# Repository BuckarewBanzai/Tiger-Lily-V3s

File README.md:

# Tiger-Lily-V3s
A breakout board for the Allwinner V3s SOC

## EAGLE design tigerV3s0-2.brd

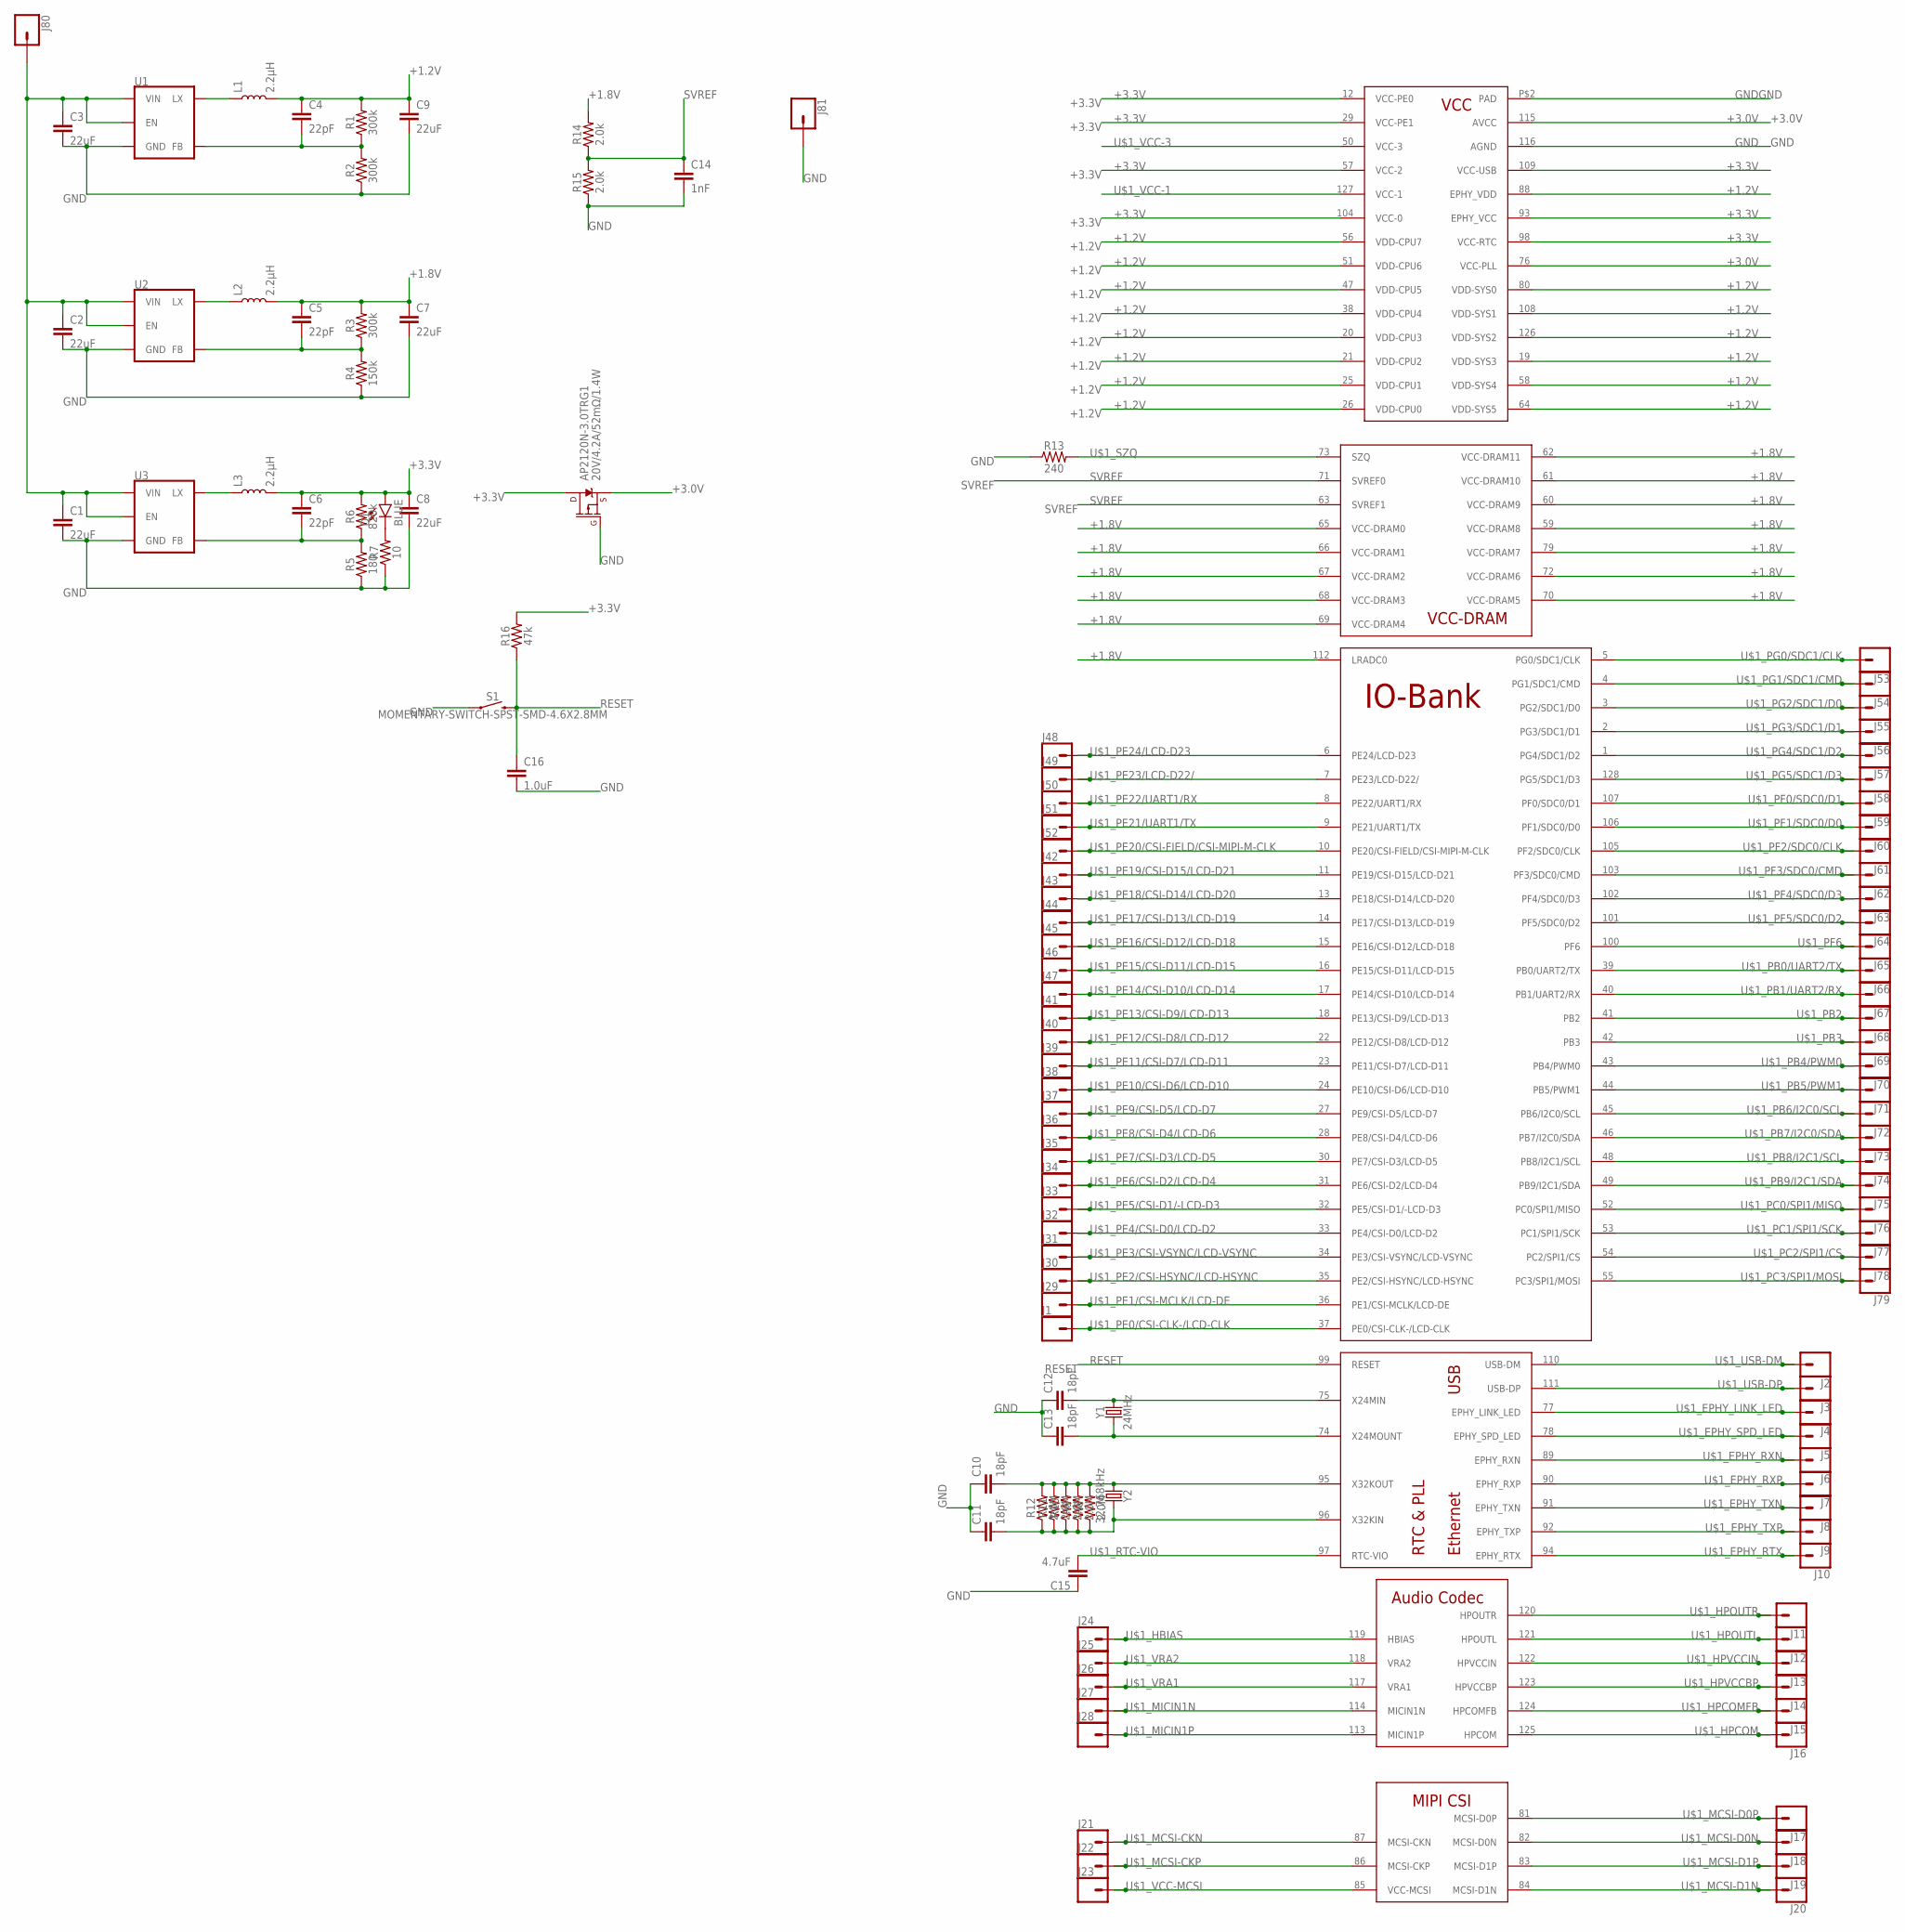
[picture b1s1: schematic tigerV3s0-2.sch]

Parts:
AP2120N-3.0TRG1: 20V/4.2A/52mΩ/1.4W; SOT23-3
C1, C2, C3, C7, C8, C9: 22uF; 0805
C4, C5, C6: 22pF; 0603
C10, C11, C12, C13: 18pF; 0603
C14: 1nF; 0603
C15: 4.7uF; 0603
C16: 1.0uF; 0603
D1: BLUE; LED-0603
J1, J2, J3, J4, J5, J6, J7, J8, J9, J10, J11, J12, J13, J14, J15, J16, J17, J18, J19, J20, J21, J22, J23, J24, J25, J26, J27, J28, J29, J30, J31, J32, J33, J34, J35, J36, J37, J38, J39, J40, J41, J42, J43, J44, J45, J46, J47, J48, J49, J50, J51, J52, J53, J54, J55, J56, J57, J58, J59, J60, J61, J62, J63, J64, J65, J66, J67, J68, J69, J70, J71, J72, J73, J74, J75, J76, J77, J78, J79, J80, J81: CONN_01; 1X01
L1, L2, L3: 2.2μH; 0805-WIDE
R1, R2, R3: 300k; 0603
R4: 150k; 0603
R5: 180; 0603
R6: 820k; 0603
R7: 10; 0603
R8, R9, R10, R11, R12: 2.0M; 0603
R13: 240; 0603
R14, R15: 2.0k; 0603
R16: 47k; 0603
S1: MOMENTARY-SWITCH-SPST-SMD-4.6X2.8MM; TACTILE_SWITCH_SMD_4.6X2.8MM
U1, U2, U3: AP3429/A; SOT23-5
U$1: V3S; QFP-128
Y1: 24MHz; CRYSTAL-SMD-5X3.2-4PAD
Y2: 32.768kHz; CRYSTAL-SMD-3.2X1.5MM

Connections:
+1.2V: C4.1, C9.1, L1.2, R1.2, U$1.19 (VDD-SYS3), U$1.20 (VDD-CPU3), U$1.21 (VDD-CPU2), U$1.25 (VDD-CPU1), U$1.26 (VDD-CPU0), U$1.38 (VDD-CPU4), U$1.47 (VDD-CPU5), U$1.51 (VDD-CPU6), U$1.56 (VDD-CPU7), U$1.58 (VDD-SYS4), U$1.64 (VDD-SYS5), U$1.80 (VDD-SYS0), U$1.88 (EPHY_VDD), U$1.108 (VDD-SYS1), U$1.126 (VDD-SYS2)
+1.8V: C5.1, C7.1, L2.2, R3.2, R14.2, U$1.59 (VCC-DRAM8), U$1.60 (VCC-DRAM9), U$1.61 (VCC-DRAM10), U$1.62 (VCC-DRAM11), U$1.65 (VCC-DRAM0), U$1.66 (VCC-DRAM1), U$1.67 (VCC-DRAM2), U$1.68 (VCC-DRAM3), U$1.69 (VCC-DRAM4), U$1.70 (VCC-DRAM5), U$1.72 (VCC-DRAM6), U$1.79 (VCC-DRAM7), U$1.112 (LRADC0)
+3.0V: AP2120N-3.0TRG1.2 (S), U$1.76 (VCC-PLL), U$1.115 (AVCC)
+3.3V: AP2120N-3.0TRG1.3 (D), C6.1, C8.1, D1.A, L3.2, R6.2, R16.2, U$1.12 (VCC-PE0), U$1.29 (VCC-PE1), U$1.57 (VCC-2), U$1.93 (EPHY_VCC), U$1.98 (VCC-RTC), U$1.104 (VCC-0), U$1.109 (VCC-USB)
+5V: C1.1, C2.1, C3.1, J80.1, U1.1 (EN), U1.4 (VIN), U2.1 (EN), U2.4 (VIN), U3.1 (EN), U3.4 (VIN)
GND: AP2120N-3.0TRG1.1 (G), C1.2, C2.2, C3.2, C7.2, C8.2, C9.2, C10.1, C11.1, C12.1, C13.1, C14.2, C15.1, C16.2, J81.1, R2.1, R4.1, R5.1, R7.1, R13.1, R15.1, S1.1, S1.2 (1), U1.2 (GND), U2.2 (GND), U3.2 (GND), U$1.116 (AGND), U$1.P$2 (PAD)
unnamed: L1.1, U1.3 (LX)
unnamed: D1.C, R7.2
unnamed: L2.1, U2.3 (LX)
unnamed: C13.2, U$1.74 (X24MOUNT), Y1.1
unnamed: L3.1, U3.3 (LX)
unnamed: C12.2, U$1.75 (X24MIN), Y1.3 (2)
unnamed: C6.2, R5.2, R6.1, U3.5 (FB)
unnamed: C5.2, R3.1, R4.2, U2.5 (FB)
unnamed: C4.2, R1.1, R2.2, U1.5 (FB)
unnamed: C10.2, R8.2, R9.2, R10.2, R11.2, R12.2, U$1.95 (X32KOUT), Y2.P$1 (1)
unnamed: C11.2, R8.1, R9.1, R10.1, R11.1, R12.1, U$1.96 (X32KIN), Y2.P$2 (2)
RESET: C16.1, R16.1, S1.3 (2), S1.4 (2), U$1.99 (RESET)
SVREF: C14.1, R14.1, R15.2, U$1.63 (SVREF1), U$1.71 (SVREF0)
U$1_EPHY_LINK_LED: J4.1, U$1.77 (EPHY_LINK_LED)
U$1_EPHY_RTX: J10.1, U$1.94 (EPHY_RTX)
U$1_EPHY_RXN: J6.1, U$1.89 (EPHY_RXN)
U$1_EPHY_RXP: J7.1, U$1.90 (EPHY_RXP)
U$1_EPHY_SPD_LED: J5.1, U$1.78 (EPHY_SPD_LED)
U$1_EPHY_TXN: J8.1, U$1.91 (EPHY_TXN)
U$1_EPHY_TXP: J9.1, U$1.92 (EPHY_TXP)
U$1_HBIAS: J24.1, U$1.119 (HBIAS)
U$1_HPCOM: J16.1, U$1.125 (HPCOM)
U$1_HPCOMFB: J15.1, U$1.124 (HPCOMFB)
U$1_HPOUTL: J12.1, U$1.121 (HPOUTL)
U$1_HPOUTR: J11.1, U$1.120 (HPOUTR)
U$1_HPVCCBP: J14.1, U$1.123 (HPVCCBP)
U$1_HPVCCIN: J13.1, U$1.122 (HPVCCIN)
U$1_MCSI-CKN: J21.1, U$1.87 (MCSI-CKN)
U$1_MCSI-CKP: J22.1, U$1.86 (MCSI-CKP)
U$1_MCSI-D0N: J18.1, U$1.82 (MCSI-D0N)
U$1_MCSI-D0P: J17.1, U$1.81 (MCSI-D0P)
U$1_MCSI-D1N: J20.1, U$1.84 (MCSI-D1N)
U$1_MCSI-D1P: J19.1, U$1.83 (MCSI-D1P)
U$1_MICIN1N: J27.1, U$1.114 (MICIN1N)
U$1_MICIN1P: J28.1, U$1.113 (MICIN1P)
U$1_PB0/UART2/TX: J66.1, U$1.39 (PB0/UART2/TX)
U$1_PB1/UART2/RX: J67.1, U$1.40 (PB1/UART2/RX)
U$1_PB2: J68.1, U$1.41 (PB2)
U$1_PB3: J69.1, U$1.42 (PB3)
U$1_PB4/PWM0: J70.1, U$1.43 (PB4/PWM0)
U$1_PB5/PWM1: J71.1, U$1.44 (PB5/PWM1)
U$1_PB6/I2C0/SCL: J72.1, U$1.45 (PB6/I2C0/SCL)
U$1_PB7/I2C0/SDA: J73.1, U$1.46 (PB7/I2C0/SDA)
U$1_PB8/I2C1/SCL: J74.1, U$1.48 (PB8/I2C1/SCL)
U$1_PB9/I2C1/SDA: J75.1, U$1.49 (PB9/I2C1/SDA)
U$1_PC0/SPI1/MISO: J76.1, U$1.52 (PC0/SPI1/MISO)
U$1_PC1/SPI1/SCK: J77.1, U$1.53 (PC1/SPI1/SCK)
U$1_PC2/SPI1/CS: J78.1, U$1.54 (PC2/SPI1/CS)
U$1_PC3/SPI1/MOSI: J79.1, U$1.55 (PC3/SPI1/MOSI)
U$1_PE0/CSI-CLK-/LCD-CLK: J1.1, U$1.37 (PE0/CSI-CLK-/LCD-CLK)
U$1_PE1/CSI-MCLK/LCD-DE: J29.1, U$1.36 (PE1/CSI-MCLK/LCD-DE)
U$1_PE2/CSI-HSYNC/LCD-HSYNC: J30.1, U$1.35 (PE2/CSI-HSYNC/LCD-HSYNC)
U$1_PE3/CSI-VSYNC/LCD-VSYNC: J31.1, U$1.34 (PE3/CSI-VSYNC/LCD-VSYNC)
U$1_PE4/CSI-D0/LCD-D2: J32.1, U$1.33 (PE4/CSI-D0/LCD-D2)
U$1_PE5/CSI-D1/-LCD-D3: J33.1, U$1.32 (PE5/CSI-D1/-LCD-D3)
U$1_PE6/CSI-D2/LCD-D4: J34.1, U$1.31 (PE6/CSI-D2/LCD-D4)
U$1_PE7/CSI-D3/LCD-D5: J35.1, U$1.30 (PE7/CSI-D3/LCD-D5)
U$1_PE8/CSI-D4/LCD-D6: J36.1, U$1.28 (PE8/CSI-D4/LCD-D6)
U$1_PE9/CSI-D5/LCD-D7: J37.1, U$1.27 (PE9/CSI-D5/LCD-D7)
U$1_PE10/CSI-D6/LCD-D10: J38.1, U$1.24 (PE10/CSI-D6/LCD-D10)
U$1_PE11/CSI-D7/LCD-D11: J39.1, U$1.23 (PE11/CSI-D7/LCD-D11)
U$1_PE12/CSI-D8/LCD-D12: J40.1, U$1.22 (PE12/CSI-D8/LCD-D12)
U$1_PE13/CSI-D9/LCD-D13: J41.1, U$1.18 (PE13/CSI-D9/LCD-D13)
U$1_PE14/CSI-D10/LCD-D14: J47.1, U$1.17 (PE14/CSI-D10/LCD-D14)
U$1_PE15/CSI-D11/LCD-D15: J46.1, U$1.16 (PE15/CSI-D11/LCD-D15)
U$1_PE16/CSI-D12/LCD-D18: J45.1, U$1.15 (PE16/CSI-D12/LCD-D18)
U$1_PE17/CSI-D13/LCD-D19: J44.1, U$1.14 (PE17/CSI-D13/LCD-D19)
U$1_PE18/CSI-D14/LCD-D20: J43.1, U$1.13 (PE18/CSI-D14/LCD-D20)
U$1_PE19/CSI-D15/LCD-D21: J42.1, U$1.11 (PE19/CSI-D15/LCD-D21)
U$1_PE20/CSI-FIELD/CSI-MIPI-M-CLK: J52.1, U$1.10 (PE20/CSI-FIELD/CSI-MIPI-M-CLK)
U$1_PE21/UART1/TX: J51.1, U$1.9 (PE21/UART1/TX)
U$1_PE22/UART1/RX: J50.1, U$1.8 (PE22/UART1/RX)
U$1_PE23/LCD-D22/: J49.1, U$1.7 (PE23/LCD-D22/)
U$1_PE24/LCD-D23: J48.1, U$1.6 (PE24/LCD-D23)
U$1_PF0/SDC0/D1: J59.1, U$1.107 (PF0/SDC0/D1)
U$1_PF1/SDC0/D0: J60.1, U$1.106 (PF1/SDC0/D0)
U$1_PF2/SDC0/CLK: J61.1, U$1.105 (PF2/SDC0/CLK)
U$1_PF3/SDC0/CMD: J62.1, U$1.103 (PF3/SDC0/CMD)
U$1_PF4/SDC0/D3: J63.1, U$1.102 (PF4/SDC0/D3)
U$1_PF5/SDC0/D2: J64.1, U$1.101 (PF5/SDC0/D2)
U$1_PF6: J65.1, U$1.100 (PF6)
U$1_PG0/SDC1/CLK: J53.1, U$1.5 (PG0/SDC1/CLK)
U$1_PG1/SDC1/CMD: J54.1, U$1.4 (PG1/SDC1/CMD)
U$1_PG2/SDC1/D0: J55.1, U$1.3 (PG2/SDC1/D0)
U$1_PG3/SDC1/D1: J56.1, U$1.2 (PG3/SDC1/D1)
U$1_PG4/SDC1/D2: J57.1, U$1.1 (PG4/SDC1/D2)
U$1_PG5/SDC1/D3: J58.1, U$1.128 (PG5/SDC1/D3)
U$1_RTC-VIO: C15.2, U$1.97 (RTC-VIO)
U$1_SZQ: R13.2, U$1.73 (SZQ)
U$1_USB-DM: J2.1, U$1.110 (USB-DM)
U$1_USB-DP: J3.1, U$1.111 (USB-DP)
U$1_VCC-1: U$1.127 (VCC-1)
U$1_VCC-3: U$1.50 (VCC-3)
U$1_VCC-MCSI: J23.1, U$1.85 (VCC-MCSI)
U$1_VRA1: J26.1, U$1.117 (VRA1)
U$1_VRA2: J25.1, U$1.118 (VRA2)

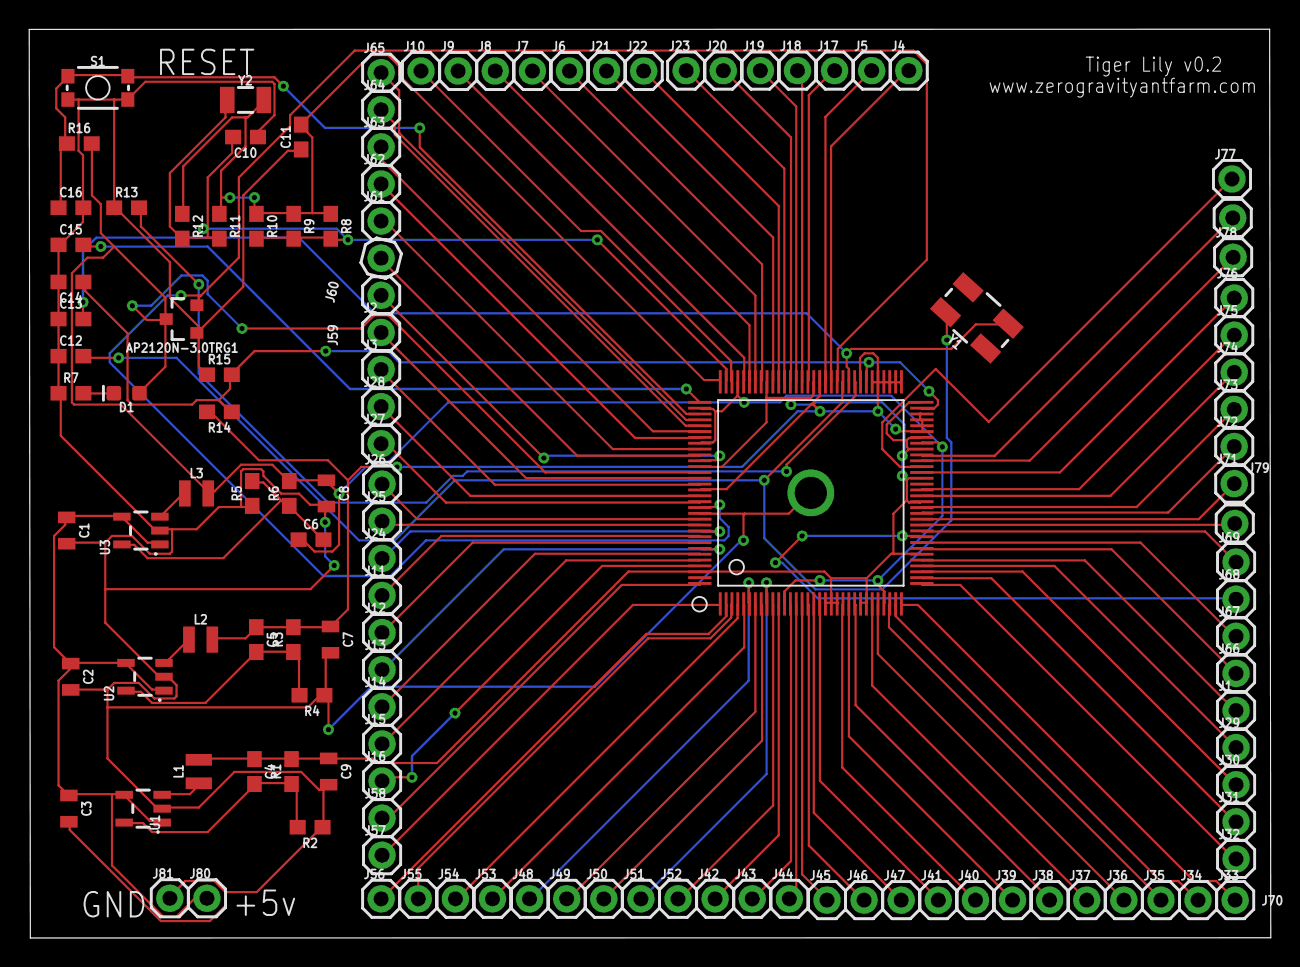
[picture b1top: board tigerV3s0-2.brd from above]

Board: 2 copper layers, 85.0 x 62.2 mm, 125 parts (0 on the bottom side), 100 nets.

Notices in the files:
parts and their libraries:
SparkFun-DiscreteSemi: Licensing: Creative Commons ShareAlike 4.0 International - https://creativecommons.org/licenses/by-sa/4.0
